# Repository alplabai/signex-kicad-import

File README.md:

# signex-kicad-import

One-way converter from KiCad boards to Signex's current native files: for
each board, `<name>.snxpcb` (format `snxpcb/1.4`) and a `<name>.snxprj`
that carries the project's net classes.

**Licensed GPL-3.0-or-later** because it implements KiCad's file
format. The Signex writer in `crates/snx-writer` is this repo's own
code, written from the format notes in `docs/SNX_FORMAT_NOTES.md`; it
does not copy Signex source. This companion tool is distributed
independently from [Signex](https://github.com/alplabai/signex).

## Usage

```bash
signex-kicad-import path/to/board.kicad_pcb            # writes board.snxpcb + board.snxprj
signex-kicad-import path/to/project.kicad_pro -o out/  # every .kicad_pcb in the project folder
signex-kicad-import --json --force board.kicad_pcb     # JSON summary, replace existing output
signex-kicad-import Device.kicad_sym -o out/                   # one symbol library, written as Device.snxsym
```

Existing output files are not replaced unless `--force` is given. Every
board is converted and checked before anything is written, so a board
that fails leaves no output. A board's two files are written together:
a `.snxpcb` never appears without its `.snxprj`, and a failed write
leaves no temporary file behind.

The summary lists what could not be carried over exactly (by kind and
count) and a self-check: how many track ends land on a pad of their own
net, and how many only on another net's pad, once Signex places the pads.

A `.kicad_sym` given without a subcommand is converted to one `<name>.snxsym`
(derived symbols, `extends`, are written as symbols of their own; what could not
be carried over is listed in the summary by message and count, like a board).
Schematic conversion is not part of this release.

For Signex's library converter contract, `signex-kicad-import describe --json`
and `signex-kicad-import library <inputs>... --output <dir>` (KiCad symbol
libraries and tables) are described in `docs/LIBRARY_CONVERTER.md`; the
`library` command converts KiCad symbol libraries and footprints into a Signex
library directory (`docs/LIBRARY_MAPPING.md`: symbols, footprints and part rows,
from files, folders or library tables; 3D STEP models are embedded).

## What the board conversion covers

- Layers mapped to Signex layer tokens (`TopCopper`, `Inner<n>Copper`,
  `BottomCopper`, `TopSilkscreen`, `EdgeCuts`, ...), the copper stack
  top to bottom with plane layers marked, and the board's own copper
  layer names kept as display names.
- The physical stackup (copper, dielectric, mask, paste and silkscreen
  rows with thickness, material, permittivity and copper weight) as the
  board's stackup rows.
- Footprints with their pads (circle, rect, oval, roundrect, trapezoid,
  and custom pads with the anchor shape and every filled primitive merged
  into one outline), drills, nets, drawings and fields. The designator
  and value texts become the Reference and Value fields. A bottom-side
  footprint is written library side up (the source's flip negates local
  y and turns the part a half turn); Signex mirrors it back.
- Tracks, copper arcs, through, blind and micro vias. Unfilled copper
  drawings become tracks and copper arcs along their stroke.
- Zones as polygon pours with their cut-outs as holes, rule areas as
  keepouts, filled copper polygons as solid copper; one zone per copper
  layer. Zones inside footprints become board zones. A hatched zone and
  a zone that leaves pads unconnected are reported.
- Arcs inside polygons (zones, custom pads, board and footprint polygons,
  the board edge) become short chords.

Anything the conversion cannot carry (3D models, text boxes, curves,
dimensions, targets, tables, hidden footprint texts, an item whose
position or size does not read) is dropped and reported by kind and
count, never dropped silently. When a file cannot be written, the
temporary files are removed and no board is written.
- The board outline: the largest closed edge ring. Other edge drawings
  (cut-outs) stay drawings on the edge layer.
- The board origin (the drill and place origin, else the grid origin).
- Net classes and board rules from the `.kicad_pro` (or the classes
  stored in older board files) into the `.snxprj`.

Item identities are kept; a missing or repeated one is replaced by a
fresh one drawn deterministically from the input, so the same input
always gives the same files.

## Tests

`crates/kicad-parser/tests/real_boards.rs` converts four real boards, one
per source format generation (6 to 9); they are listed with their
licences in `crates/kicad-parser/tests/fixtures/README.md`.

The writers for `.snxsym`, `.snxfpt` and the `.snxlib` manifest are checked
against the Signex library format's conformance fixtures, which belong to the
Signex repository and are not copied here:

```bash
SIGNEX_FORMAT_FIXTURES=/path/to/signex/docs/fixtures/library-format \
  cargo test -p snx-writer --test library_conformance
```

Without the variable those tests print a skip message and pass.

## Install

From source:
```bash
cargo install --path crates/cli
```

## License

GPL-3.0-or-later. See `LICENSE`.

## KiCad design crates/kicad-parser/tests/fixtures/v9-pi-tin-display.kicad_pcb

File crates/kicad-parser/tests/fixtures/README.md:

# Board fixtures

Real boards, one per source format generation, used by `tests/real_boards.rs`.
They are third-party designs under their own licences (the licence files sit
beside them); they are not covered by this repository's licence.

| File | Format version | Source (pinned commit) | Licence |
|---|---|---|---|
| `v6-rp2040-designguide.kicad_pcb` | 20211014 | https://github.com/calliah333/RP2040-designguide at a9afaa2ea5ee9d859ef126d919c607737a75eb30, `PCB/RP2040-Guide.kicad_pcb` | MIT, `LICENSE-RP2040-designguide` |
| `v7-microwave-probe.kicad_pcb` | 20221018 | https://github.com/AndyShor/Open-microwave-probe at fba1f81c80c555c0b5a6b677589ec57c7ca6960c, `electromagnetic_probe.kicad_pcb` | MIT, `LICENSE-Open-microwave-probe` |
| `v8-n64-expansion-pak.kicad_pcb` | 20240108 | https://github.com/MasonStooksbury/OEM-N64-Expansion-Pak at 52a64944c587962353d0510712d9dfd0f23767b1, `OriginalN64ExpansionPak.kicad_pcb` | CERN-OHL-P-2.0, `LICENSE-OEM-N64-Expansion-Pak` |
| `v9-pi-tin-display.kicad_pcb` | 20241229 | https://github.com/jackw01/pi-tin at 3c433e58ce99d202a0605d67e0e0df8a3e012e38, `pcb_display_r2a/displaypcb.kicad_pcb` | CERN-OHL-W-2.0, `LICENSE-pi-tin` |

The files are unmodified copies.

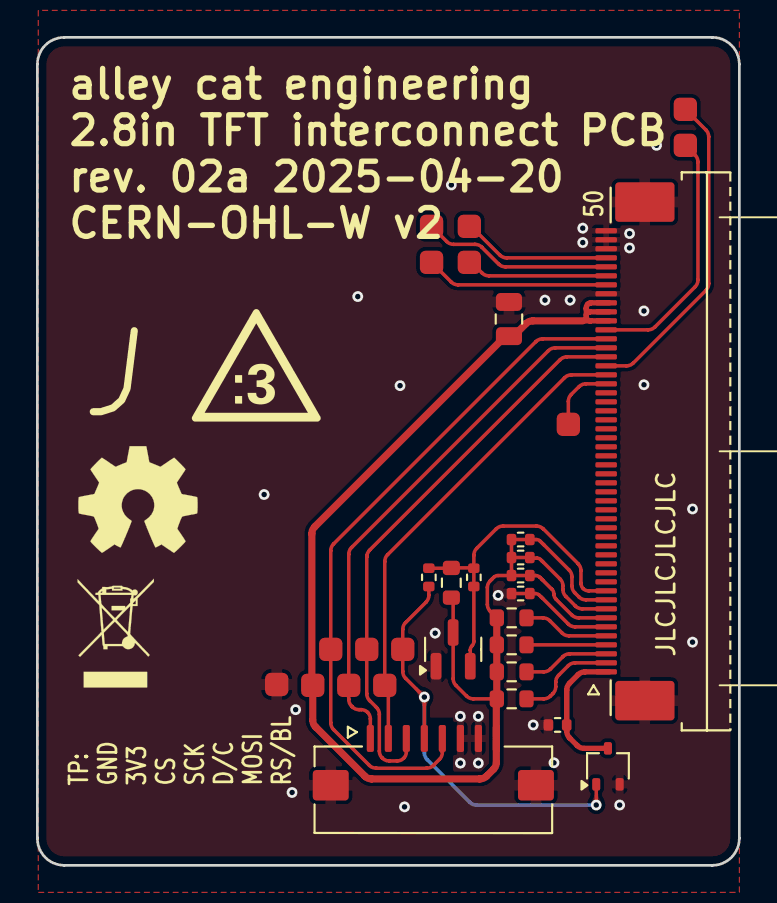
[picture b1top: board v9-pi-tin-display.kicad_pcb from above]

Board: 2 copper layers, 39.0 x 46.0 mm, 32 parts (1 on the bottom side), 25 nets.

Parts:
C101: 10u; C_0805_2012Metric
J102: FPC09-Q1.0-8AH2.0; XYECONN_FPC09-Q1.0-8AH2.0
J103: AFC07-S50ECA-00; Jushuo_AFC07-S50ECA-00
JP101, JP103, JP104, JP105, JP106: SolderJumper_2_Bridged; R_0402_1005Metric_bridged
JP102, JP107: SolderJumper_2_Open; R_0402_1005Metric
N101: Display; TFT_2.8in_ILI9341
Q101: CJ3134KW; SOT-323_SC-70
R101, R102, R103, R105: 10; R_0603_1608Metric
R104: 10k; R_0603_1608Metric
TP101, TP102, TP103, TP104, TP105, TP106, TP107, TP108, TP109, TP110, TP111, TP112, TP113, TP114: TestPoint_Small; TestPoint_Pad_D1.5mm
U101: APX803-31SAG; SOT-23

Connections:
+3.3V: C101.1, J102.8, J103.40, J103.41, J103.42, JP104.1 (A), JP105.1 (A), JP106.1 (A), R101.2, R102.2, R103.2, R104.1, R105.2, TP102.1, U101.3 (VCC)
/D/C: J102.3, J103.36, TP107.1
/IM0: J103.6, JP103.2 (B)
/IM1: J103.7, JP104.2 (B)
/IM2: J103.8, JP105.2 (B)
/IM3: J103.9, JP106.2 (B)
/LEDA1: J103.2, R105.1
/LEDA2: J103.3, R103.1
/LEDA3: J103.4, R102.1
/LEDA4: J103.5, R101.1
/LEDK: J103.1, JP102.2 (B), Q101.3 (D)
/RD: J103.35, TP106.1
/RESET: J103.10, JP101.2 (B), JP107.2 (B), R104.2
/RS/BL: J102.4, JP107.1 (A), Q101.1 (G), TP103.1
/SPI_CS: J102.5, J103.38, TP109.1
/SPI_MISO: J103.33, TP104.1
/SPI_MOSI: J102.2, J103.34, TP105.1
/SPI_SCK: J102.1, J103.37, TP108.1
/TE: J103.39, TP110.1
/XL: J103.46, TP113.1
/XR: J103.44, TP111.1
/YD: J103.45, TP112.1
/YU: J103.47, TP114.1
GND: C101.2, J102.6, J102.7, J102.MP (MountPin), J103.43, J103.48, J103.49, J103.50, J103.MP (MountPin), JP102.1 (A), JP103.1 (A), Q101.2 (S), TP101.1, U101.1 (GND)
unnamed: JP101.1 (A), U101.2 (~RESET)

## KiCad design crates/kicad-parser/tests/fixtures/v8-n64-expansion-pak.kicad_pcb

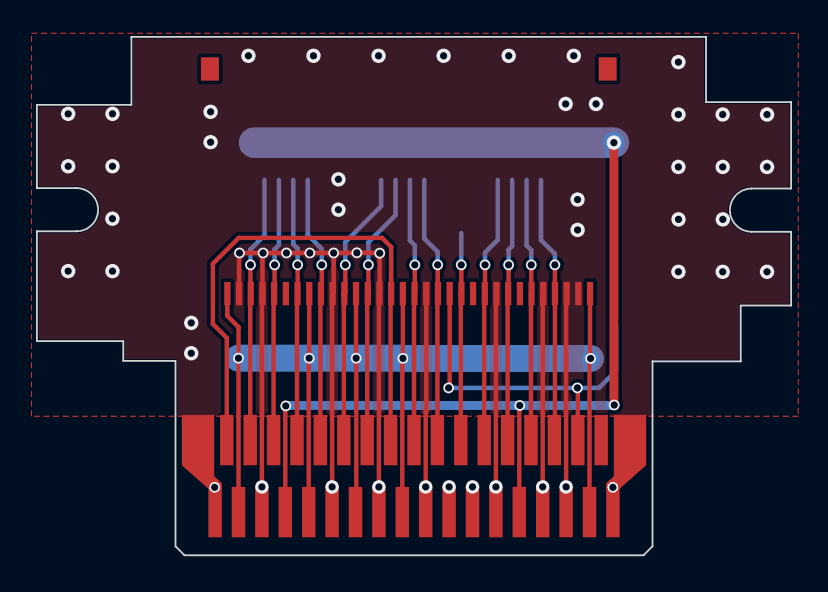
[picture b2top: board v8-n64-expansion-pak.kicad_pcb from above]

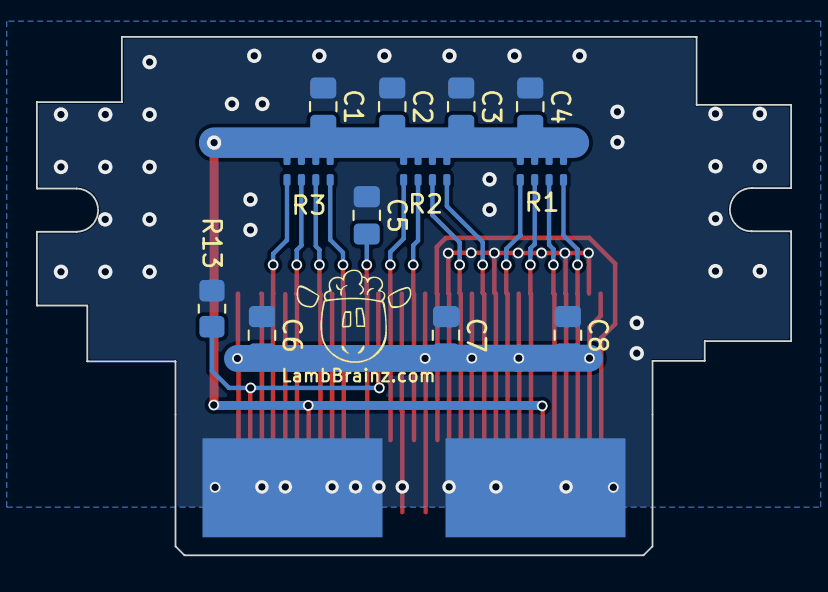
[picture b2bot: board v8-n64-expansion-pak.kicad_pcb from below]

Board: 2 copper layers, 41.9 x 28.8 mm, 14 parts (12 on the bottom side), 18 nets.

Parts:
C1, C2, C3, C4, C5, C6, C7, C8: KEMET C0805C185K8PAC7800; C_0805_2012Metric_Pad1.18x1.45mm_HandSolder
R1, R2, R3: Panasonic EXB-V8V510JV; Resistor Array
R13: Yageo RC0805FR-07510RL; R_0805_2012Metric_Pad1.20x1.40mm_HandSolder
U1: MSM5718B70-60GS-K; RAM Module
U2: Expansion Pak Edge Connector; EdgeConnector

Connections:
GND: C1.1, C2.1, C3.1, C4.1, C5.1, C6.1, C7.1, C8.1, R13.1, U1.2 (GND), U1.4 (GND), U1.10 (GND), U1.14 (GND_A), U1.18 (GND), U1.24 (GND), U1.28 (GND), U1.30 ((NC)), U1.31 (GND), U2.0, U2.4, U2.10, U2.14, U2.18, U2.20, U2.22, U2.24, U2.28, U2.30, U2.34, U2.-
unnamed: C1.2, C2.2, C3.2, C4.2, R1.5 (2), R1.6 (2), R1.7 (2), R1.8 (2), R2.5 (2), R2.6 (2), R2.7 (2), R2.8 (2), R3.5 (2), R3.6 (2), R3.7 (2), R3.8 (2), U2.6, U2.26
unnamed: C5.2, U1.21 (V_REF), U2.21
unnamed: C6.2, C7.2, C8.2, U1.1 (V_DD), U1.8 (V_DD), U1.12 (V_DDA), U1.16 (V_DD), U1.32 (V_DD), U2.2, U2.8, U2.12, U2.16, U2.32
unnamed: R1.1, U1.3 (BusData8), U2.3
unnamed: R1.2 (1), U1.5 (BusData7), U2.5
unnamed: R1.3 (1), U1.7 (BusEnable), U2.7
unnamed: R1.4 (1), U1.9 (BusData6), U2.9
unnamed: R2.1, U1.11 (BusData5), U2.11
unnamed: R2.2 (1), U1.13 (Rx_Clk), U2.13
unnamed: R2.3 (1), U1.17 (BusData4), U2.17
unnamed: R2.4 (1), U1.19 (BusCtrl), U2.19
unnamed: R3.1, U1.23 (BusData3), U2.23
unnamed: R3.2 (1), U1.25 (BusData2), U2.25
unnamed: R3.3 (1), U1.27 (BusData1), U2.27
unnamed: R3.4 (1), U1.29 (BusData0), U2.29
unnamed: R13.2, U1.20 (S_In), U2.31
unnamed: U1.15 (Tx_Clk), U2.1, U2.15

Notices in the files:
crates/kicad-parser/tests/fixtures/v9-pi-tin-display.kicad_pcb:
CERN-OHL-W v2
Released under the CERN-OHL-W V2 license
